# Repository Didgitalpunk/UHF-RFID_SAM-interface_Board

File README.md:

# UHF-RFID SAM interface Board
A PCB for connecting UHF-RFID readers to your flipper, and a SEC1210 iC to allow you to interface and use a SAM.
Also has a 6 pin ICSP header and an SPI header to use with various FAPs.

This board is made for the flipper zero and uses https://github.com/frux-c/uhf_rfid for the UHF-RFID part, and https://github.com/bettse/seader for the SAM part.
The SPI and ICSP headers on this board are here for use with the SPI_Mem_Manager fap, and the AVR_Flasher fap respectively, among, I'm sure, others faps.

Thanks to the UHF|RFID gang over on the flipper zero discord for all the nice comments, all the info, and especially, the initial push on the UHF|RFID project!

This repository is meant to be used as a reference for users to be able to build/debug their own boards. Making boards for you and your friends is absolutely permitted.
If you want to make my board for yourself or free distribution, I only ask you keep the links present on the boards linking to this repository, as well as my name.
Comercial sales of boards ***using my design*** are not allowed unless you contact me first and we reach an agreement.

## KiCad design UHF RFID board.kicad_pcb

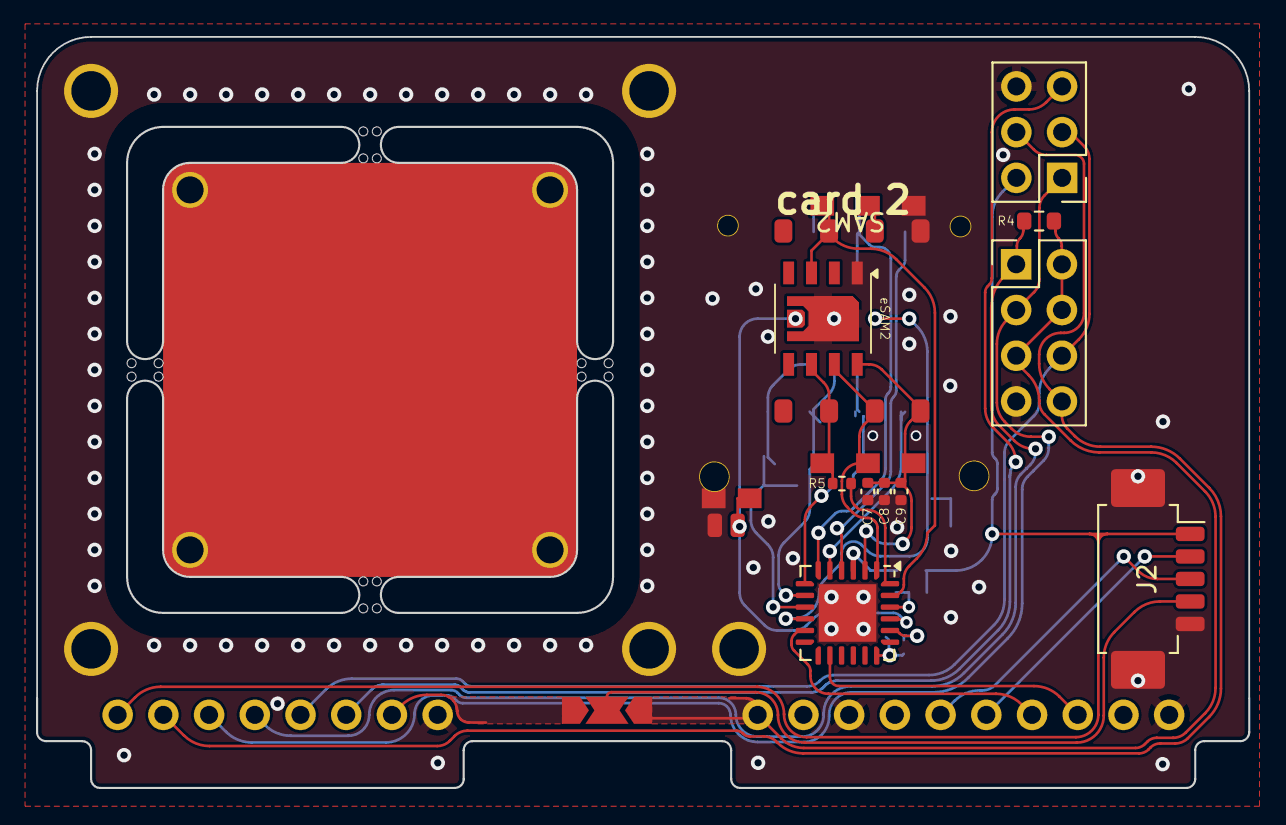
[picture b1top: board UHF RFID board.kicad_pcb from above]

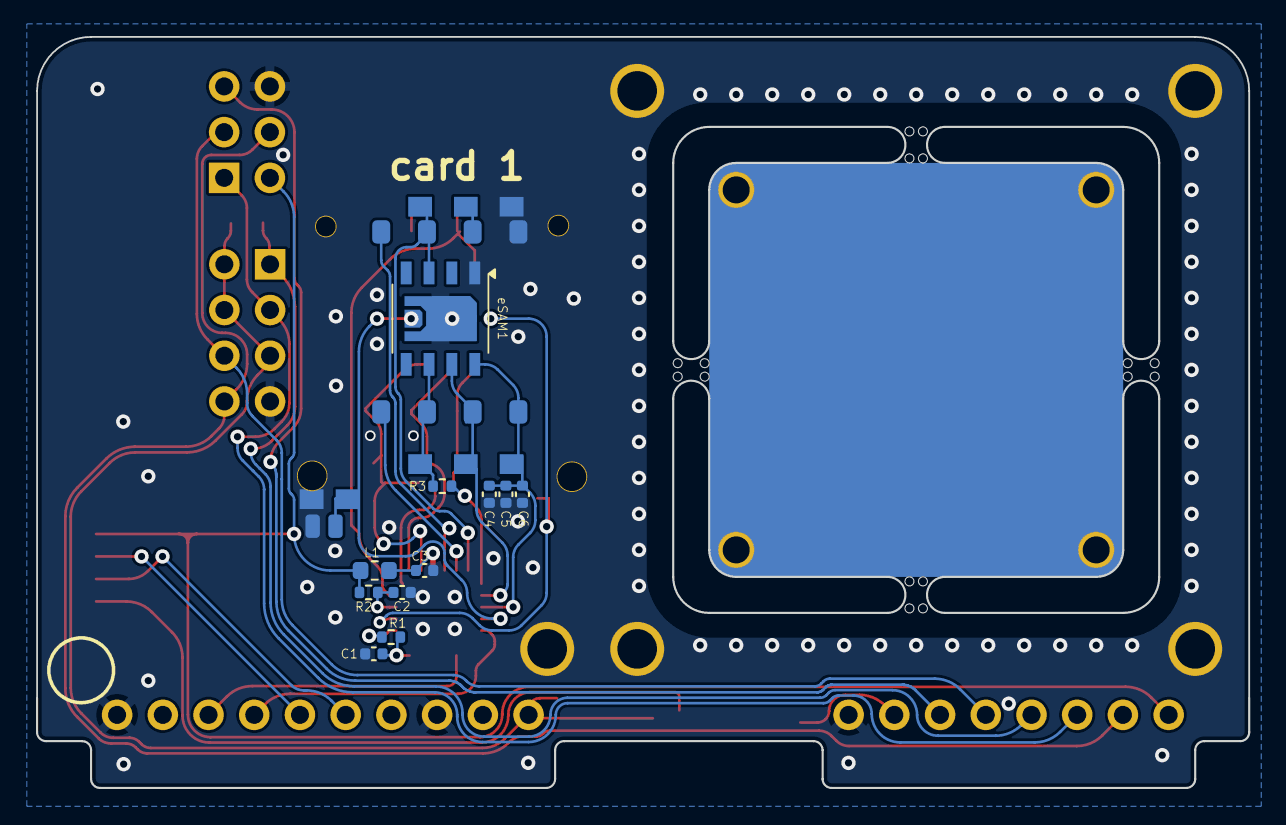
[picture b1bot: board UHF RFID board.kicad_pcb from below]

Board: 2 copper layers, 67.3 x 41.7 mm, 28 parts (13 on the bottom side), 32 nets.

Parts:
C1, C3, C5, C8: 1uF; C_0402_1005Metric
C2, C6, C9: 0.1uF; C_0402_1005Metric
C4, C7: 10uF; C_0402_1005Metric
J1: FZ_full_module; FZ full module
J2: picoblade; Molex_PicoBlade_53261-0571_1x05-1MP_P1.25mm_Horizontal
J3: SPI; PinHeader_2x04_P2.54mm_Vertical
J4: ICSP; PinHeader_2x03_P2.54mm_Vertical
JP1: SolderJumper_3_Open; SolderJumper-3_P2.0mm_Open_TrianglePad1.0x1.5mm
L1: 2A/0.05DCR; L_0603_1608Metric
R1: 1M; R_0402_1005Metric
R2: 100K; R_0402_1005Metric
R3, R5: 43R; R_0402_1005Metric
R4: 10k; R_0603_1608Metric
SAM1, SAM2: SIM_Card; SIMMP-00801B000-G + 711S1615A01LF
U1: YRM1001; UHF_RFID_35x35_YRM1001_module_through-board no_header with 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
U2: SEC1210; QFN-24-1EP_5x5mm_P0.65mm_EP3.2x3.2mm
[Seader] repo by Bettse: [Seader] repo by Bettse
[UHF | RFID for Flipper] repo by Frux: [UHF RFID for Flipper] repo by Frux
eSAM1, eSAM2: DFN-8-splitEP_5x5mm_P1.27mm_EP2.5x4mm

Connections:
+3.3V: J1.9 (3V3), J3.2, J3.4, J3.5, JP1.3 (B), R4.1
+3.3VA: C1.1, R1.2, U2.18 (VDD33)
+5V: J1.1 (5V), J2.1, J4.2, L1.1, R2.1
/EN: J2.4, JP1.2 (C)
/LED_ACT: R1.1, U2.20 (SC_LED_ACT_N/JTAG_TDO)
/PC0: J1.16 (C0), U2.14 (SPI1_MOSI/TXD)
/PC1: J1.15 (C1), U2.11 (SPI1_MISO/RXD)
/PC3: J1.7 (C3), JP1.1 (A)
/SC1_C4: SAM1.4 (C4), U2.5 (SC1_C4)
/SC1_C8: SAM1.8 (C8), U2.4 (SC1_C8)
/SC1_CLK: R3.2, SAM1.3 (CLK), eSAM1.6 (CLK)
/SC1_IO: SAM1.7 (I/O), U2.6 (SC1_IO), eSAM1.3 (SC_IO)
/SC1_PRSNT: SAM1.CSW (detect), U2.10 (SC1_PRSNT_N/JTAG_TMS), eSAM1.9 (PRSNT)
/SC1_RST: SAM1.2 (RST), U2.8 (SC1_RST_N), eSAM1.7 (RST)
/SC1_VCC: C4.1, C5.1, C6.1, SAM1.1 (VCC), U2.9 (SC1_VCC), eSAM1.8 (VCC)
/SC2_CLK: R5.2, SAM2.3 (CLK), eSAM2.6 (CLK)
/SC2_IO: SAM2.7 (I/O), U2.23 (SC2_IO), eSAM2.3 (SC_IO)
/SC2_PRsNT: SAM2.CSW (detect), U2.21 (SC2_PRSNT_N/JTAG_TDI), eSAM2.9 (PRSNT)
/SC2_RST: SAM2.2 (RST), U2.1 (SC2_RST_N), eSAM2.7 (RST)
/SC2_VCC: C7.2, C8.2, C9.2, SAM2.1 (VCC), U2.2 (SC2_VCC), eSAM2.8 (VCC)
/UART_RX: J1.14 (RX), J2.2
/UART_TX: J1.13 (TX), J2.3
/VDD5: C3.1, L1.2, U2.3 (VDD5)
/~RESET: C2.1, R2.2, U2.22 (~RESET)
CLK: J1.5 (B3), J3.6, J4.3
CS: J1.4 (A4), J3.1, R4.2
GND: C1.2, C2.2, C3.2, C4.2, C5.2, C6.2, C7.1, C8.1, C9.1, J1.8 (GND), J1.11 (GND), J1.18 (GND), J2.5, J2.MP, J3.7, J4.6, SAM1.5 (GND), SAM1.DSW (detect), SAM2.5 (GND), SAM2.DSW (detect), U1.5 (mounting), U2.25 (VSS(flag)), eSAM1.1 (GND), eSAM2.1 (GND)
MISO: J1.3 (A6), J3.3, J4.1
MOSI: J1.2 (A7), J3.8, J4.4
unnamed: R3.1, U2.7 (SC1_CLK)
unnamed: R5.1, U2.24 (SC2_CLK)
RST: J1.6 (B2), J4.5

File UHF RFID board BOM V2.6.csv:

Reference,Value,Footprint,Qty,DNP,#,Digikey,mouser
C1 C3 C5 C8,1uF,Capacitor_SMD:C_0402_1005Metric,4,,1,,https://www.mouser.fr/ProductDetail/Murata-Electronics/GRM15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
C2 C6 C9,0.1uF,Capacitor_SMD:C_0402_1005Metric,3,,2,,https://www.mouser.fr/ProductDetail/581-KGM05AR51A104KH
C4 C7,10uF,Capacitor_SMD:C_0402_1005Metric,2,,3,,https://www.mouser.fr/ProductDetail/81-GRM155R61A106ME1J
J1a,FZ_full_module,Flipper modules:FZ full module,1,,4,,https://www.mouser.fr/ProductDetail/855-M20-9960845
J1b,FZ_full_module,Flipper modules:FZ full module,1,,5,,https://www.mouser.fr/ProductDetail/855-M20-9961045
J2,picoblade,Connector_Molex:Molex_PicoBlade_53261-0571_1x05-1MP_P1.25mm_Horizontal,1,,6,,https://www.mouser.fr/ProductDetail/Molex/53261-0571?qs=Z4et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
J3,SPI,Connector_PinHeader_2.54mm:PinHeader_2x04_P2.54mm_Vertical,1,,7,,https://www.mouser.fr/ProductDetail/Harwin/M20-9950445?qs=WS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
J4,ICSP,Connector_PinHeader_2.54mm:PinHeader_2x03_P2.54mm_Vertical,1,,8,,https://www.mouser.fr/ProductDetail/Harwin/M20-9950345?qs=%2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
L1,2A/0.05DCR,Inductor_SMD:L_0603_1608Metric,1,,9,,https://www.mouser.fr/ProductDetail/Murata-Electronics/BLM18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
R1,1M,Resistor_SMD:R_0402_1005Metric,1,,10,,https://www.mouser.fr/ProductDetail/652-CR0402FX-1004GLF
R2,100K,Resistor_SMD:R_0402_1005Metric,1,,11,,https://www.mouser.fr/ProductDetail/Bourns/CR0402-FX-1003GLF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
R3 R5,43R,Resistor_SMD:R_0402_1005Metric,2,,12,,https://www.mouser.fr/ProductDetail/Bourns/CR0402-FX-43R0GLF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
R4,10k,Resistor_SMD:R_0603_1608Metric,1,,13,,https://www.mouser.fr/ProductDetail/652-CR0603-JW-103ELF
SAM1 SAM2,SIM_Card,Custom footprints:SIMMP-00801B000-G + 711S1615A01LF,2,,14,https://www.digikey.com/en/products/detail/amphenol-cs-fci/7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,https://www.mouser.fr/ProductDetail/Amphenol-FCI/7111S1615A0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
U2,SEC1210,Package_DFN_QFN:QFN-24-1EP_5x5mm_P0.65mm_EP3.2x3.2mm,1,,15,,https://www.mouser.fr/ProductDetail/Microchip-Technology/SEC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

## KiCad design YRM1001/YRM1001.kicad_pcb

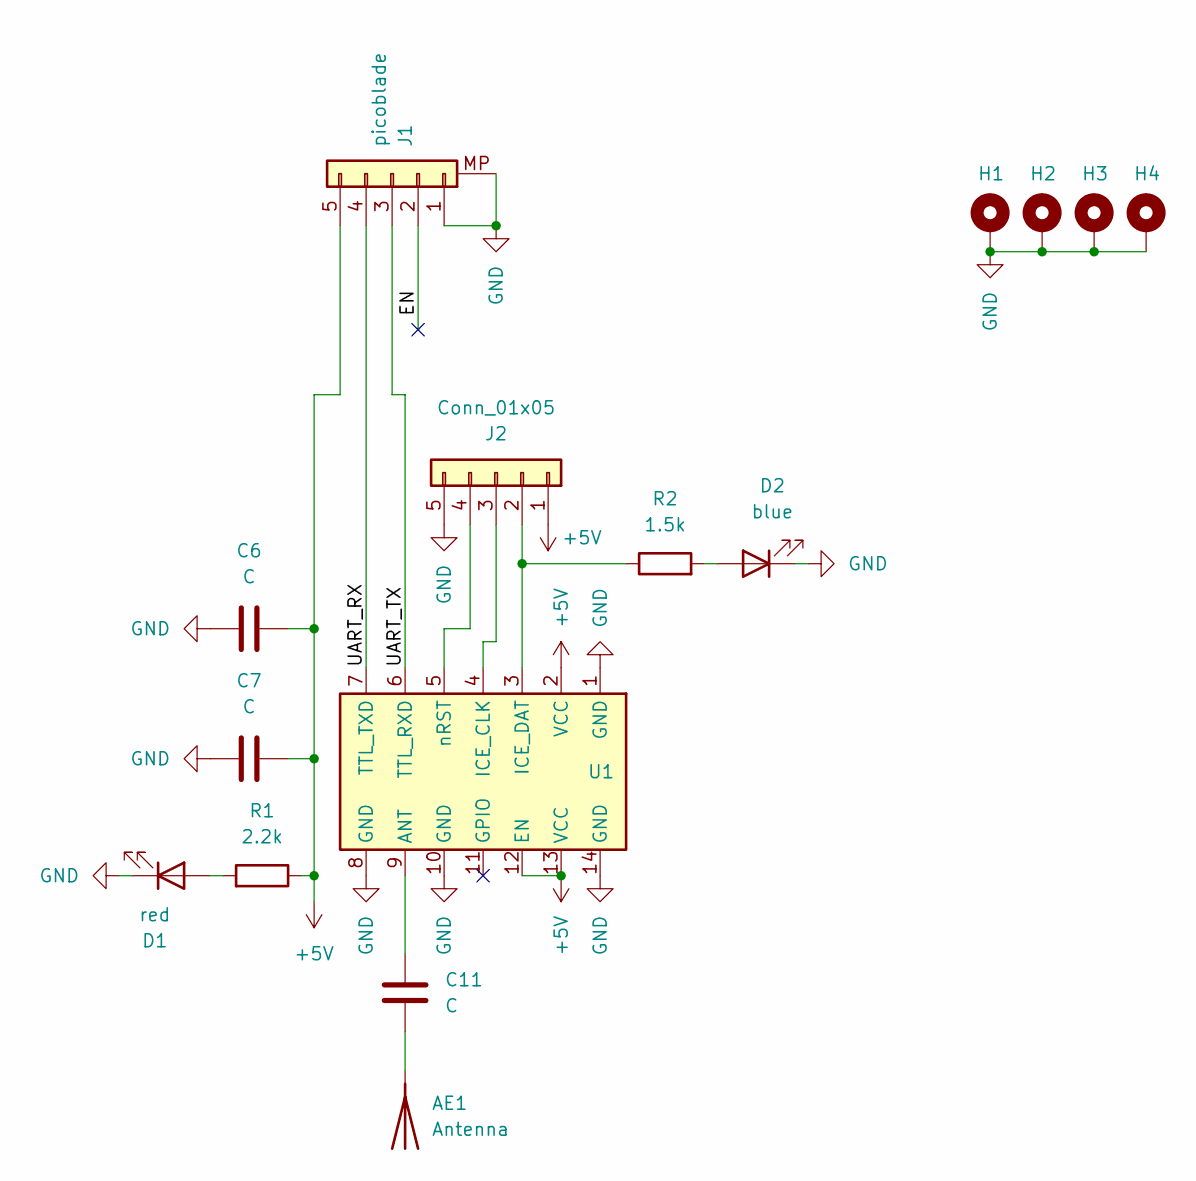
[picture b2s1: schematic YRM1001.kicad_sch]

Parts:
AE1: Antenna; UHF_RFID_25x25_antenna
C6, C7, C11: C; C_0805_2012Metric_Pad1.18x1.45mm_HandSolder
D1: red; LED_0805_2012Metric_Pad1.15x1.40mm_HandSolder
D2: blue; LED_0805_2012Metric_Pad1.15x1.40mm_HandSolder
H1, H2, H3, H4: MountingHole_Pad; MountingHole_2.2mm_M2_ISO7380_Pad
J1: picoblade; Molex_PicoBlade_53261-0571_1x05-1MP_P1.25mm_Horizontal
J2: Conn_01x05; PinHeader_1x05_P2.54mm_Vertical
R1: 2.2k; R_0805_2012Metric_Pad1.20x1.40mm_HandSolder
R2: 1.5k; R_0805_2012Metric_Pad1.20x1.40mm_HandSolder
U1: YRM200

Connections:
+5V: C6.1, C7.1, J1.5, J2.1, R1.1, U1.2 (VCC), U1.12 (EN), U1.13 (VCC)
/EN: J1.2
/UART_RX: J1.4, U1.7 (TTL_TXD)
/UART_TX: J1.3, U1.6 (TTL_RXD)
GND: C6.2, C7.2, D1.1 (K), D2.1 (K), H1.1, H2.1, H3.1, H4.1, J1.1, J1.MP, J2.5, U1.1 (GND), U1.8 (GND), U1.10 (GND), U1.14 (GND)
unnamed: AE1.1 (A), C11.1
unnamed: D1.2 (A), R1.2
unnamed: D2.2 (A), R2.2
unnamed: J2.2, R2.1, U1.3 (ICE_DAT)
unnamed: J2.3, U1.4 (ICE_CLK)
unnamed: J2.4, U1.5 (nRST)
unnamed: C11.2, U1.9 (ANT)

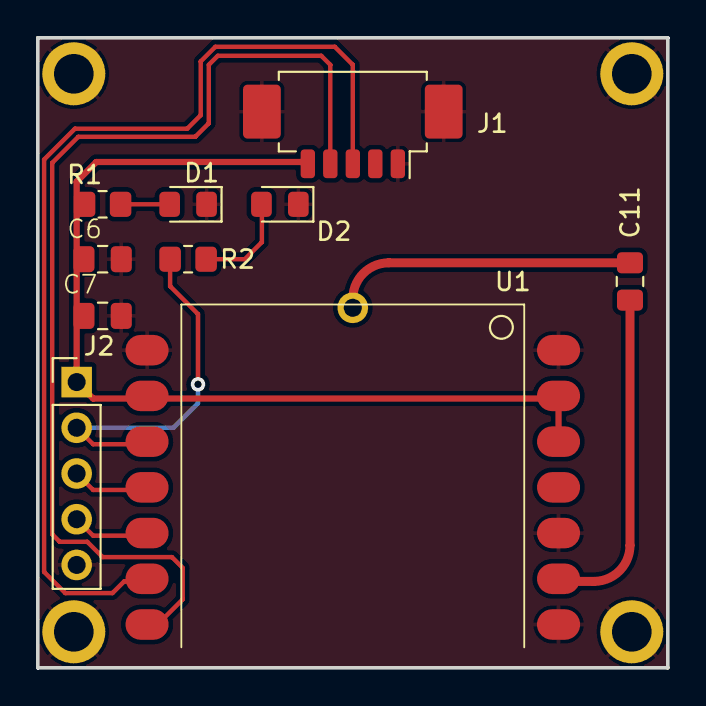
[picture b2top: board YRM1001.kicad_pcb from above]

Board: 2 copper layers, 35.0 x 35.0 mm, 15 parts (1 on the bottom side), 11 nets.

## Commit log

2023-12-10 added board files. V1.1
    Added kicad files for V1.1
    Changes from (unrealeased) V1.0 > V1.1:
    - spread out D+ and D- labels to ensure no shorts are made if you try and solder to the D+ and D- lines
    - re-poured ground plane so L1 no longer shorts 5V to ground on both sides because of a non-updated ground pour
    - added name and version on top of board
    - re-routed pin header for YRM1001 since the connector was pinned differently than anticipated. none of the pins are duplicates of the picoblade connector save for ground and +5V
2023-12-10 Update README.md
    added ICSP and SPI header info
2023-12-10 Update README.md
    .
2023-12-10 added case 3D model
    added case 3D model V1.0
2023-12-10 Added YRM1001 board files
    YRM1001 board reverse-engineering
2023-12-10 changed the footprint for SIM card to the correct one
2023-12-10 Added important datasheets
2023-12-10 added more info and thanks in the README.md
2023-12-12 removed mentions of nard board on suggestion of the UHF|RFID gang
2024-01-15 Add files via upload
    updated board version to 1.2:
    - changed ICSP from 10 pin header to 6 pin header. 10 pin ICSP connections can be done with a 6 to 10 pin adapter cable.
    - changed name on board to UHF | RFID | SAM, removing '1/2 nard' from the name for clarity on what the board is and does.
    - removed header that was meant to hard-connect the UHF module to the board: it is not used for communication with the board after all.
    - updated the QR codes designs for better machine readability
    - various routing improvements.
2024-01-16 Version 2.0 RELEASE
    - removed M3 support hole for 50x50 modules: there was only one M3 hole anyway, so no good mechanical support. case for the board can designed with mounting holes for that size module if need be.
    - added second SAM slot as per SEC1210 datasheet.
    - rerouted the vast majority of the board to accommodate all the changes.
    - changed board thickness to 1.2 from 1.6 as per Flipper Zero module specs
    - repositioned the SAM slots close to the board edge for ease of access to the SAMs with a case on.
    - repositioned all of the components needed for the SEC1210 for addition of second SAM slot
2024-01-16 Updated README.md
    changed 10 pin ICSP to 6 pin ICSP
2024-01-17 finalization for V2.0 board production aspect
    - specified adhesive layers for all the back-mounted components
    - added footprint and model for kapton tape over USB breakout vias
2024-02-02 Update V2.1
    - modified schematic to add iClass SE processor chip connections and symbol
    - added footprints to enable direct mounting of iClass SE processor chips instead of using a SAM (https://www.hidglobal.com/products/sio-processor)
    - added e.e.
    - routing
2024-02-02 Update README.md
    changed NARD mention to SAM. slipped between the cracks last time.
2024-02-18 fixes + bom, end of work on V2
    Fixed some footprint directory inconsistencies and errors dating form at least the start of the SAM integration phase for some, Cleaned up / reworked some footprints and finalized others.
    Fixed some BOM links being incorrect and/or missing.
    That concludes work on V2. Next additions will go towards V3 if there ever is one, but the board is now getting very cramped, and will be in a branch now that I know how those work.
2024-02-18 added case files for V2 board
    added closed and open bottoms, insert and nuts versions, top, large antenna version, pin cover and main design files
2024-02-23 added V1 board pictures
    Added front and back pictures for V1 board
2024-03-03 V2.3 release
    Switched a resistor and capacitor to B.cu to ensure they don't get ripped off when removing the picoblade connector. depending on further testing to see if I can get the LEDout working on the SEC chi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
    Cleaned up routing a bit due to that change.
2024-03-03 fixed some rounded tracks that were no longer arcs
2024-03-04 removed no longer needed features (LEDs, USB)
    After testing it turns out the USB port on the SEC1210 UART version does not seem to be enabled. Therefore there's no way to program the chip to enable the LED output.
    Removed unneeded D1, D2, R6, and re-positioned R1 and C1 thanks to the extra space.
    updated schematic with DNP tags for D1, D2, R6.
2024-03-12 futureproofing for automated production
    Added fiducial markers for automated PNP machine assembly capability.
    updated version from 2.4 to 2.5
    added version info in schematic, along with title and my name for credit
2024-04-29 ease of assembly update
    added pin 1 marker on silkscreen for eSAM footprints, previously pin 1 was denoted by a chamfer in the center pad
2024-05-09 V2.5.2 production update
    - removed unused + out-of-bounds mounting holes for the yrm1003 module that could throw errors in fab houses
    - corrected SIMMP-00801B000-G sim slot footprint, fab outline was bigger than the part, and model was not accurate for the part.
2024-05-09 V2.5.3 yrm footprint center pad corner rounding
2024-05-15 Version 2.5.4 - copper to board edge fix
    copper to board edge clearance was erroneously set to 0 instead of .254mm . PCB still functioned fine, this is purely to aid manufacturing and prevent manufacturers from throwing errors at you.
2025-04-21 V2.6.0
    - flipped the inputs of the picoblade connector, so there's no longer a need for a pass-through cable which in hindsight, good. it seemed dumb a long time ago, but you live and learn. Now the off-the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
    - nudged the whole SAM stuff 1mm higher, which should no longer hinder connecting/disconnecting the picoblade cable in some cases.
    (previously if a SIM slot was soldered in CARD 2, the connector would barely hit the end of the SIM slot. Now it doesn't.)
    - updated board version number to V2.6.0
2025-10-01 footprint, updated BOM. staying at release 2.6.0
    added secondary footprint for the SIM slot to use a sim slot that's still available (amphenol 7111S1615A01LF )
2025-10-01 Delete UHF RFID board V2.2.csv
    removed old BOM file
2026-01-28 Update README with usage and distribution guidelines
    Clarify usage terms for the board design and distribution.
    (this commit message was created by copilot, but it's a good description)
